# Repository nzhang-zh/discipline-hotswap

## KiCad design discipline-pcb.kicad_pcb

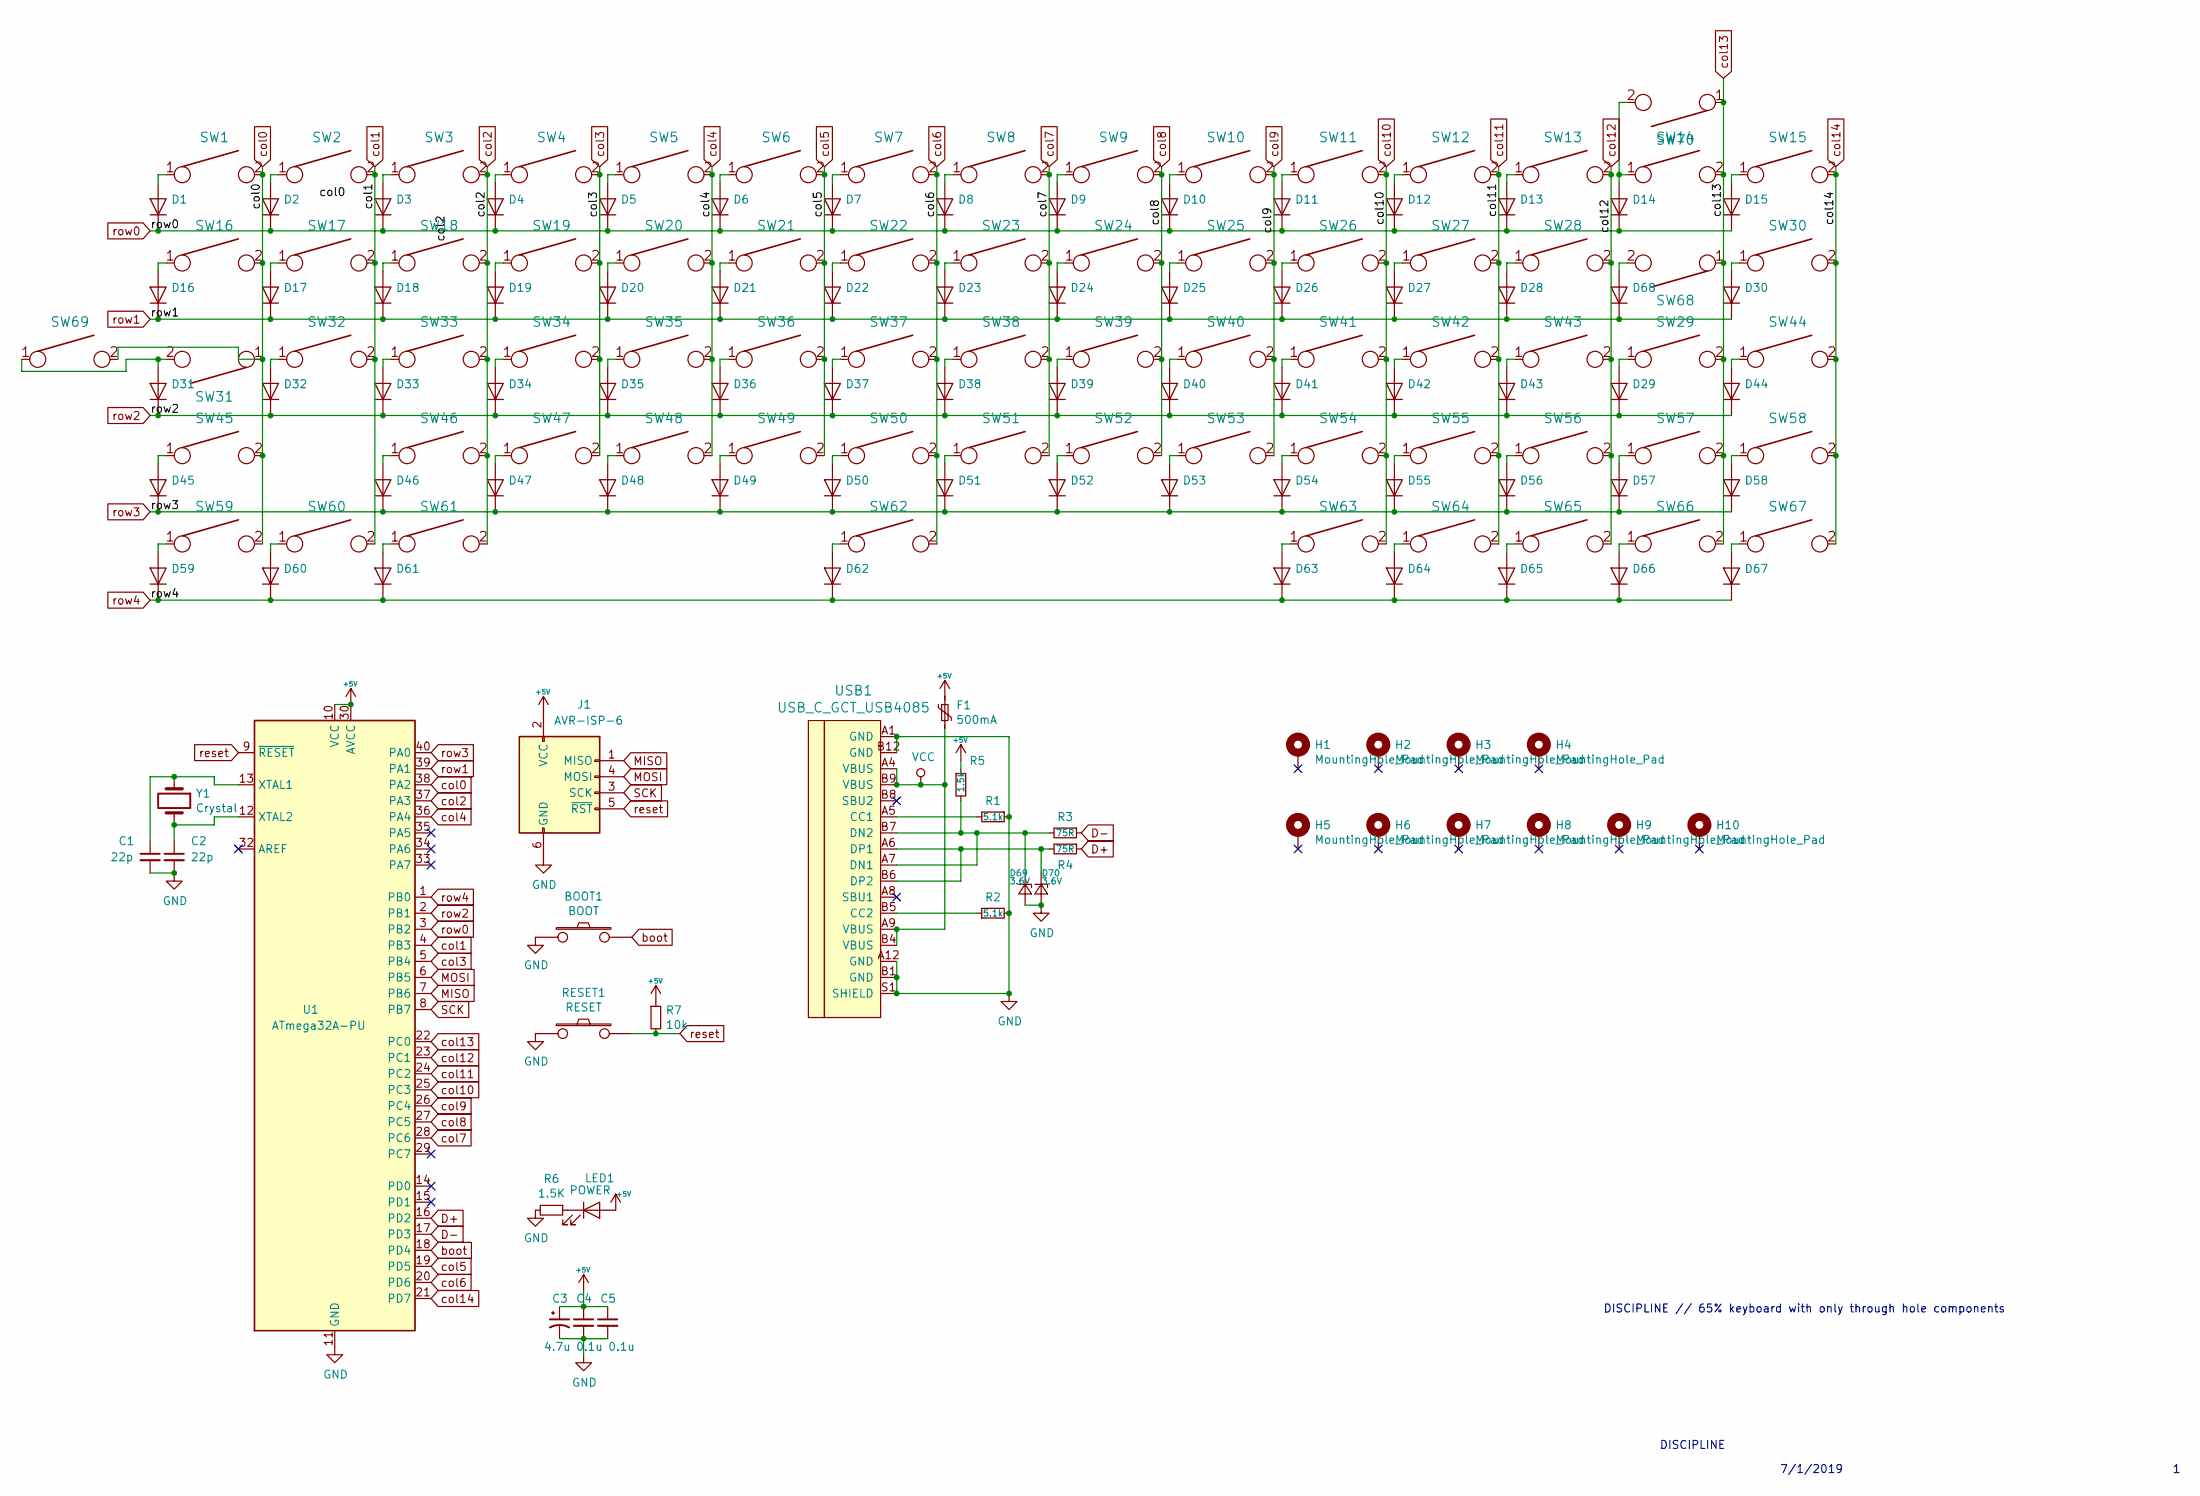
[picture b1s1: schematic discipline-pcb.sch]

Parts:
BOOT1: BOOT; SW_PUSH_6mm
C1, C2: 22p; D_DO-35_SOD27_P5.08mm_Horizontal
C3: 4.7u; D_DO-35_SOD27_P5.08mm_Horizontal
C4, C5: 0.1u; D_DO-35_SOD27_P5.08mm_Horizontal
D1, D2, D3, D4, D5, D6, D7, D8, D9, D10, D11, D12, D13, D14, D15, D16, D17, D18, D19, D20, D21, D22, D23, D24, D25, D26, D27, D28, D29, D30, D31, D32, D33, D34, D35, D36, D37, D38, D39, D40, D41, D42, D43, D44, D45, D46, D47, D48, D49, D50, D51, D52, D53, D54, D55, D56, D57, D58, D59, D60, D61, D62, D63, D64, D65, D66, D67, D68: D_DO-35_SOD27_P5.08mm_Horizontal
D69, D70: 3.6V; D_DO-35_SOD27_P5.08mm_Horizontal
F1: 500mA; polyfuse_5.1mm
H1, H2, H3, H4, H5, H6, H7, H8, H9, H10: MountingHole_Pad; MountingHole_2.2mm_M2_Pad_Via
J1: AVR-ISP-6; AVR_ICSP_3x2
LED1: POWER; LED_D3.0mm
R1, R2: 5.1k; R_Axial_DIN0204_L3.6mm_D1.6mm_P7.62mm_Horizontal
R3, R4: 75R; R_Axial_DIN0204_L3.6mm_D1.6mm_P7.62mm_Horizontal
R5: 1.5k; R_Axial_DIN0204_L3.6mm_D1.6mm_P7.62mm_Horizontal
R6: 1.5K; R_Axial_DIN0204_L3.6mm_D1.6mm_P7.62mm_Horizontal
R7: 10k; R_Axial_DIN0204_L3.6mm_D1.6mm_P7.62mm_Horizontal
RESET1: RESET; SW_PUSH_6mm
SW1, SW2, SW3, SW4, SW5, SW6, SW7, SW8, SW9, SW10, SW11, SW12, SW13, SW15, SW17, SW18, SW19, SW20, SW21, SW22, SW23, SW24, SW25, SW26, SW27, SW28, SW30, SW32, SW33, SW34, SW35, SW36, SW37, SW38, SW39, SW40, SW41, SW42, SW44, SW46, SW47, SW48, SW49, SW50, SW51, SW52, SW53, SW54, SW55, SW57, SW58, SW60, SW65, SW66, SW67, SW68, SW70: KEYSW; MXOnly-1U-Hotswap
SW14: KEYSW; MXOnly-2U-Hotswap
SW16, SW29: KEYSW; MXOnly-1.5U-Hotswap
SW31, SW56: KEYSW; MXOnly-1.75U-Hotswap
SW43, SW45: KEYSW; MXOnly-2.25U-Hotswap
SW59, SW61, SW63, SW64, SW69: KEYSW; MXOnly-1.25U-Hotswap
SW62: KEYSW; MXOnly-7U-Hotswap-ReversedStabilizers
U1: ATmega32A-PU; DIP-40_W15.24mm
USB1: USB_C_GCT_USB4085
Y1: Crystal; Crystal_HC49-4H_Vertical

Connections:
+5V: C3.1, C4.1, C5.1, F1.1, J1.2 (VCC), LED1.2 (A), R5.1, R7.1, U1.10 (VCC), U1.30 (AVCC)
D+: R4.1, U1.16 (PD2)
D-: R3.1, U1.17 (PD3)
GND: BOOT1.1, C1.2, C2.2, C3.2, C4.2, C5.2, D69.2 (A), D70.2 (A), J1.6 (GND), R1.1, R2.2, R6.2, RESET1.1, U1.11 (GND), U1.31 (GND), USB1.A1 (GND), USB1.A12 (GND), USB1.B1 (GND), USB1.B12 (GND), USB1.S1 (SHIELD)
MISO: J1.1 (MISO), U1.7 (PB6)
MOSI: J1.4 (MOSI), U1.6 (PB5)
unnamed: C1.1, U1.13 (XTAL1), Y1.1
unnamed: C2.1, U1.12 (XTAL2), Y1.2
unnamed: D1.2 (A), SW1.1
unnamed: D2.2 (A), SW2.1
unnamed: D3.2 (A), SW3.1
unnamed: D4.2 (A), SW4.1
unnamed: D5.2 (A), SW5.1
unnamed: D6.2 (A), SW6.1
unnamed: D7.2 (A), SW7.1
unnamed: D8.2 (A), SW8.1
unnamed: D9.2 (A), SW9.1
unnamed: D10.2 (A), SW10.1
unnamed: D11.2 (A), SW11.1
unnamed: D12.2 (A), SW12.1
unnamed: D13.2 (A), SW13.1
unnamed: D14.2 (A), SW14.1, SW70.2
unnamed: D15.2 (A), SW15.1
unnamed: D16.2 (A), SW16.1
unnamed: D17.2 (A), SW17.1
unnamed: D18.2 (A), SW18.1
unnamed: D19.2 (A), SW19.1
unnamed: D20.2 (A), SW20.1
unnamed: D21.2 (A), SW21.1
unnamed: D22.2 (A), SW22.1
unnamed: D23.2 (A), SW23.1
unnamed: D24.2 (A), SW24.1
unnamed: D25.2 (A), SW25.1
unnamed: D26.2 (A), SW26.1
unnamed: D27.2 (A), SW27.1
unnamed: D28.2 (A), SW28.1
unnamed: D29.2 (A), SW29.1
unnamed: D30.2 (A), SW30.1
unnamed: D31.2 (A), SW31.2, SW69.1
unnamed: D32.2 (A), SW32.1
unnamed: D33.2 (A), SW33.1
unnamed: D34.2 (A), SW34.1
unnamed: D35.2 (A), SW35.1
unnamed: D36.2 (A), SW36.1
unnamed: D37.2 (A), SW37.1
unnamed: D38.2 (A), SW38.1
unnamed: D39.2 (A), SW39.1
unnamed: D40.2 (A), SW40.1
unnamed: D41.2 (A), SW41.1
unnamed: D42.2 (A), SW42.1
unnamed: D43.2 (A), SW43.1
unnamed: D44.2 (A), SW44.1
unnamed: D45.2 (A), SW45.1
unnamed: D46.2 (A), SW46.1
unnamed: D47.2 (A), SW47.1
unnamed: D48.2 (A), SW48.1
unnamed: D49.2 (A), SW49.1
unnamed: D50.2 (A), SW50.1
unnamed: D51.2 (A), SW51.1
unnamed: D52.2 (A), SW52.1
unnamed: D53.2 (A), SW53.1
unnamed: D54.2 (A), SW54.1
unnamed: D55.2 (A), SW55.1
unnamed: D56.2 (A), SW56.1
unnamed: D57.2 (A), SW57.1
unnamed: D58.2 (A), SW58.1
unnamed: D59.2 (A), SW59.1
unnamed 67: D60.2 (A), SW60.1; also elsewhere on the board
unnamed 68: D61.2 (A), SW61.1; also elsewhere on the board
unnamed 69: D62.2 (A), SW62.1; also elsewhere on the board
unnamed 70: D63.2 (A), SW63.1; also elsewhere on the board
unnamed 71: D64.2 (A), SW64.1; also elsewhere on the board
unnamed: D65.2 (A), SW65.1
unnamed: D66.2 (A), SW66.1
unnamed: D67.2 (A), SW67.1
unnamed: D68.2 (A), SW68.2
unnamed: D69.1 (K), R3.2, R5.2, USB1.A7 (DN1), USB1.B7 (DN2)
unnamed: D70.1 (K), R4.2, USB1.A6 (DP1), USB1.B6 (DP2)
unnamed: LED1.1 (K), R6.1
unnamed: R1.2, USB1.A5 (CC1)
unnamed: R2.1, USB1.B5 (CC2)
SCK: J1.3 (SCK), U1.8 (PB7)
VCC: F1.2, USB1.A4 (VBUS), USB1.A9 (VBUS), USB1.B4 (VBUS), USB1.B9 (VBUS)
boot: BOOT1.2, U1.18 (PD4)
col0: SW1.2, SW16.2, SW31.1, SW45.2, SW59.2, SW69.2, U1.38 (PA2)
col1: SW2.2, SW17.2, SW32.2, SW60.2, U1.4 (PB3); also elsewhere on the board
col2: SW3.2, SW18.2, SW33.2, SW46.2, SW61.2, U1.37 (PA3); also elsewhere on the board
col3: SW4.2, SW19.2, SW34.2, SW47.2, U1.5 (PB4)
col4: SW5.2, SW20.2, SW35.2, SW48.2, U1.36 (PA4)
col5: SW6.2, SW21.2, SW36.2, SW49.2, U1.19 (PD5)
col6: SW7.2, SW22.2, SW37.2, SW50.2, SW62.2, U1.20 (PD6); also elsewhere on the board
col7: SW8.2, SW23.2, SW38.2, SW51.2, U1.28 (PC6)
col8: SW9.2, SW24.2, SW39.2, SW52.2, U1.27 (PC5)
col9: SW10.2, SW25.2, SW40.2, SW53.2, U1.26 (PC4)
col10: SW11.2, SW26.2, SW41.2, SW54.2, SW63.2, U1.25 (PC3); also elsewhere on the board
col11: SW12.2, SW27.2, SW42.2, SW55.2, SW64.2, U1.24 (PC2); also elsewhere on the board
col12: SW13.2, SW28.2, SW43.2, SW56.2, SW65.2, U1.23 (PC1)
col13: SW14.2, SW29.2, SW57.2, SW66.2, SW68.1, SW70.1, U1.22 (PC0)
col14: SW15.2, SW30.2, SW44.2, SW58.2, SW67.2, U1.21 (PD7)
reset: J1.5 (~RST), R7.2, RESET1.2, U1.9 (~RESET)
row0: D1.1 (K), D2.1 (K), D3.1 (K), D4.1 (K), D5.1 (K), D6.1 (K), D7.1 (K), D8.1 (K), D9.1 (K), D10.1 (K), D11.1 (K), D12.1 (K), D13.1 (K), D14.1 (K), D15.1 (K), U1.3 (PB2)
row1: D16.1 (K), D17.1 (K), D18.1 (K), D19.1 (K), D20.1 (K), D21.1 (K), D22.1 (K), D23.1 (K), D24.1 (K), D25.1 (K), D26.1 (K), D27.1 (K), D28.1 (K), D30.1 (K), D68.1 (K), U1.39 (PA1)
row2: D29.1 (K), D31.1 (K), D32.1 (K), D33.1 (K), D34.1 (K), D35.1 (K), D36.1 (K), D37.1 (K), D38.1 (K), D39.1 (K), D40.1 (K), D41.1 (K), D42.1 (K), D43.1 (K), D44.1 (K), U1.2 (PB1)
row3: D45.1 (K), D46.1 (K), D47.1 (K), D48.1 (K), D49.1 (K), D50.1 (K), D51.1 (K), D52.1 (K), D53.1 (K), D54.1 (K), D55.1 (K), D56.1 (K), D57.1 (K), D58.1 (K), U1.40 (PA0)
row4: D59.1 (K), D60.1 (K), D61.1 (K), D62.1 (K), D63.1 (K), D64.1 (K), D65.1 (K), D66.1 (K), D67.1 (K), U1.1 (PB0)

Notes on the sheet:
DISCIPLINE // 65% keyboard with only through hole components
7/1/2019
DISCIPLINE

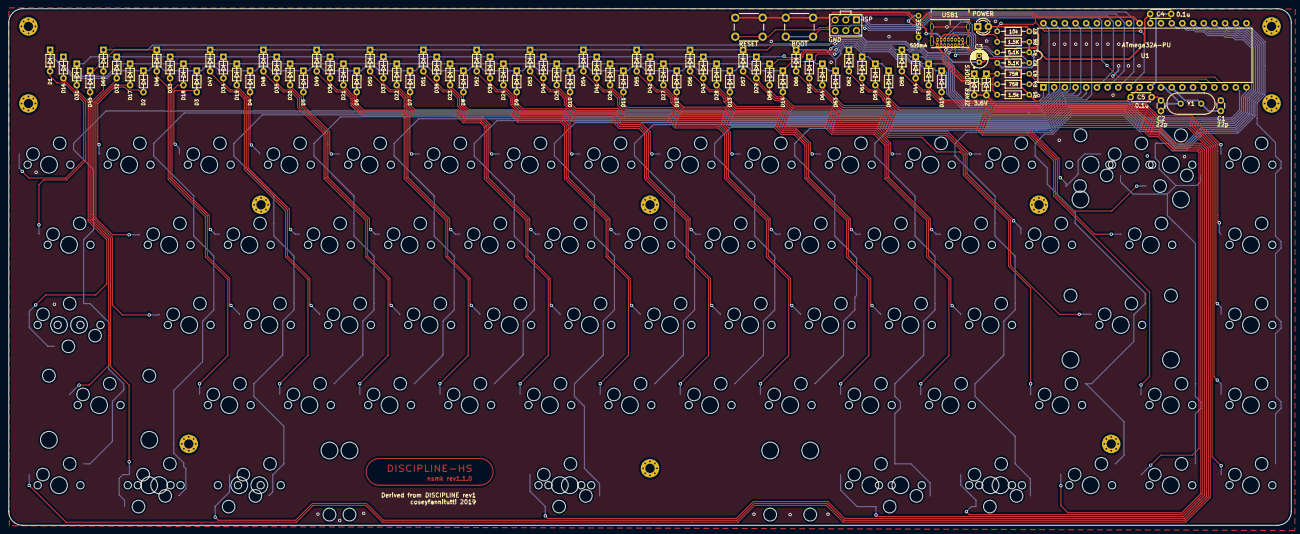
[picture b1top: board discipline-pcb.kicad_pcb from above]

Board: 2 copper layers, 304.9 x 122.8 mm, 175 parts (0 on the bottom side), 105 nets.

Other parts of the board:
SW71: KEYSW; MXOnly-7U-Hotswap
SW72, SW73, SW75: KEYSW; MXOnly-1.25U-Hotswap
SW74: KEYSW; MXOnly-1U-Hotswap

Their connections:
unnamed 67: SW74.2; also elsewhere on the board
unnamed 68: SW75.2; also elsewhere on the board
unnamed 69: SW71.2; also elsewhere on the board
unnamed 70: SW72.2; also elsewhere on the board
unnamed 71: SW73.2; also elsewhere on the board
col1: SW74.1; also elsewhere on the board
col2: SW75.1; also elsewhere on the board
col6: SW71.1; also elsewhere on the board
col10: SW72.1; also elsewhere on the board
col11: SW73.1; also elsewhere on the board

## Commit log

2020-04-05 Initial hotswap version
2020-04-06 Add alternative bottom row
